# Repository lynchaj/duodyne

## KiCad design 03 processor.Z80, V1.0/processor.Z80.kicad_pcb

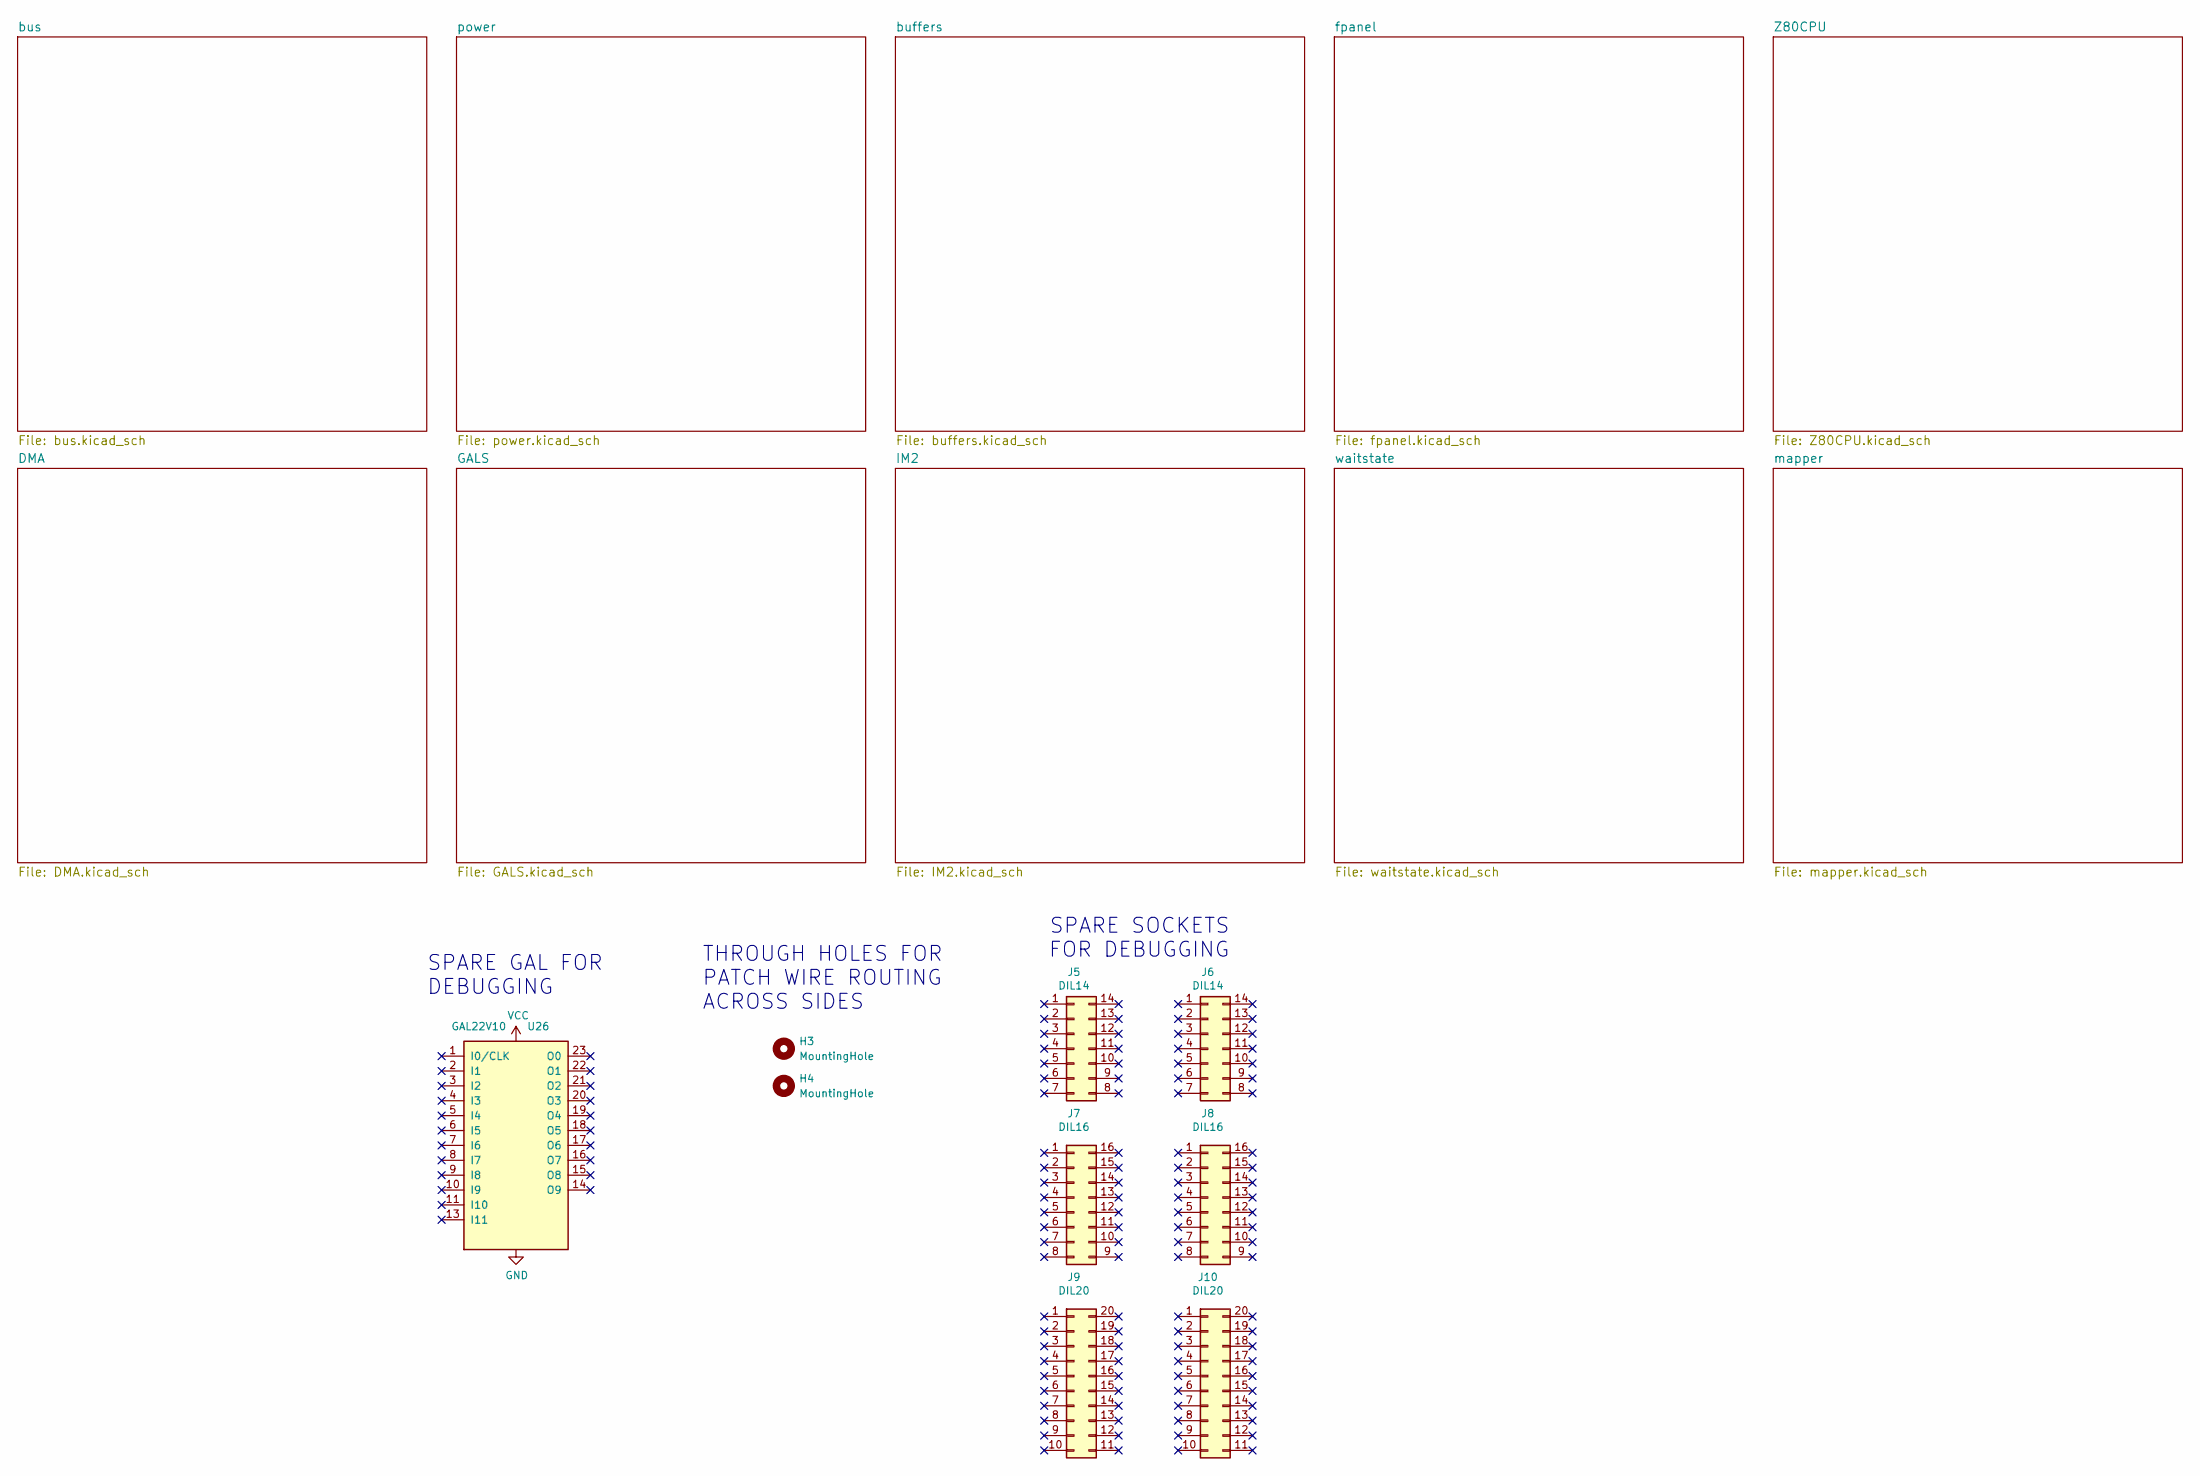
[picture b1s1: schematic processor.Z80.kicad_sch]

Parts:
H3, H4: MountingHole; MountingHole_2.2mm_M2_DIN965_Pad
J5, J6: DIL14; DIP-14_W7.62mm
J7, J8: DIL16; DIP-16_W7.62mm
J9, J10: DIL20; DIP-20_W7.62mm
U26: GAL22V10; DIP-24_W7.62mm

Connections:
GND: U26.12 (GND); also elsewhere on the board
VCC: U26.24 (VCC); also elsewhere on the board

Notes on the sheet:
THROUGH HOLES FOR PATCH WIRE ROUTING ACROSS SIDES
SPARE GAL FOR DEBUGGING
SPARE SOCKETS FOR DEBUGGING

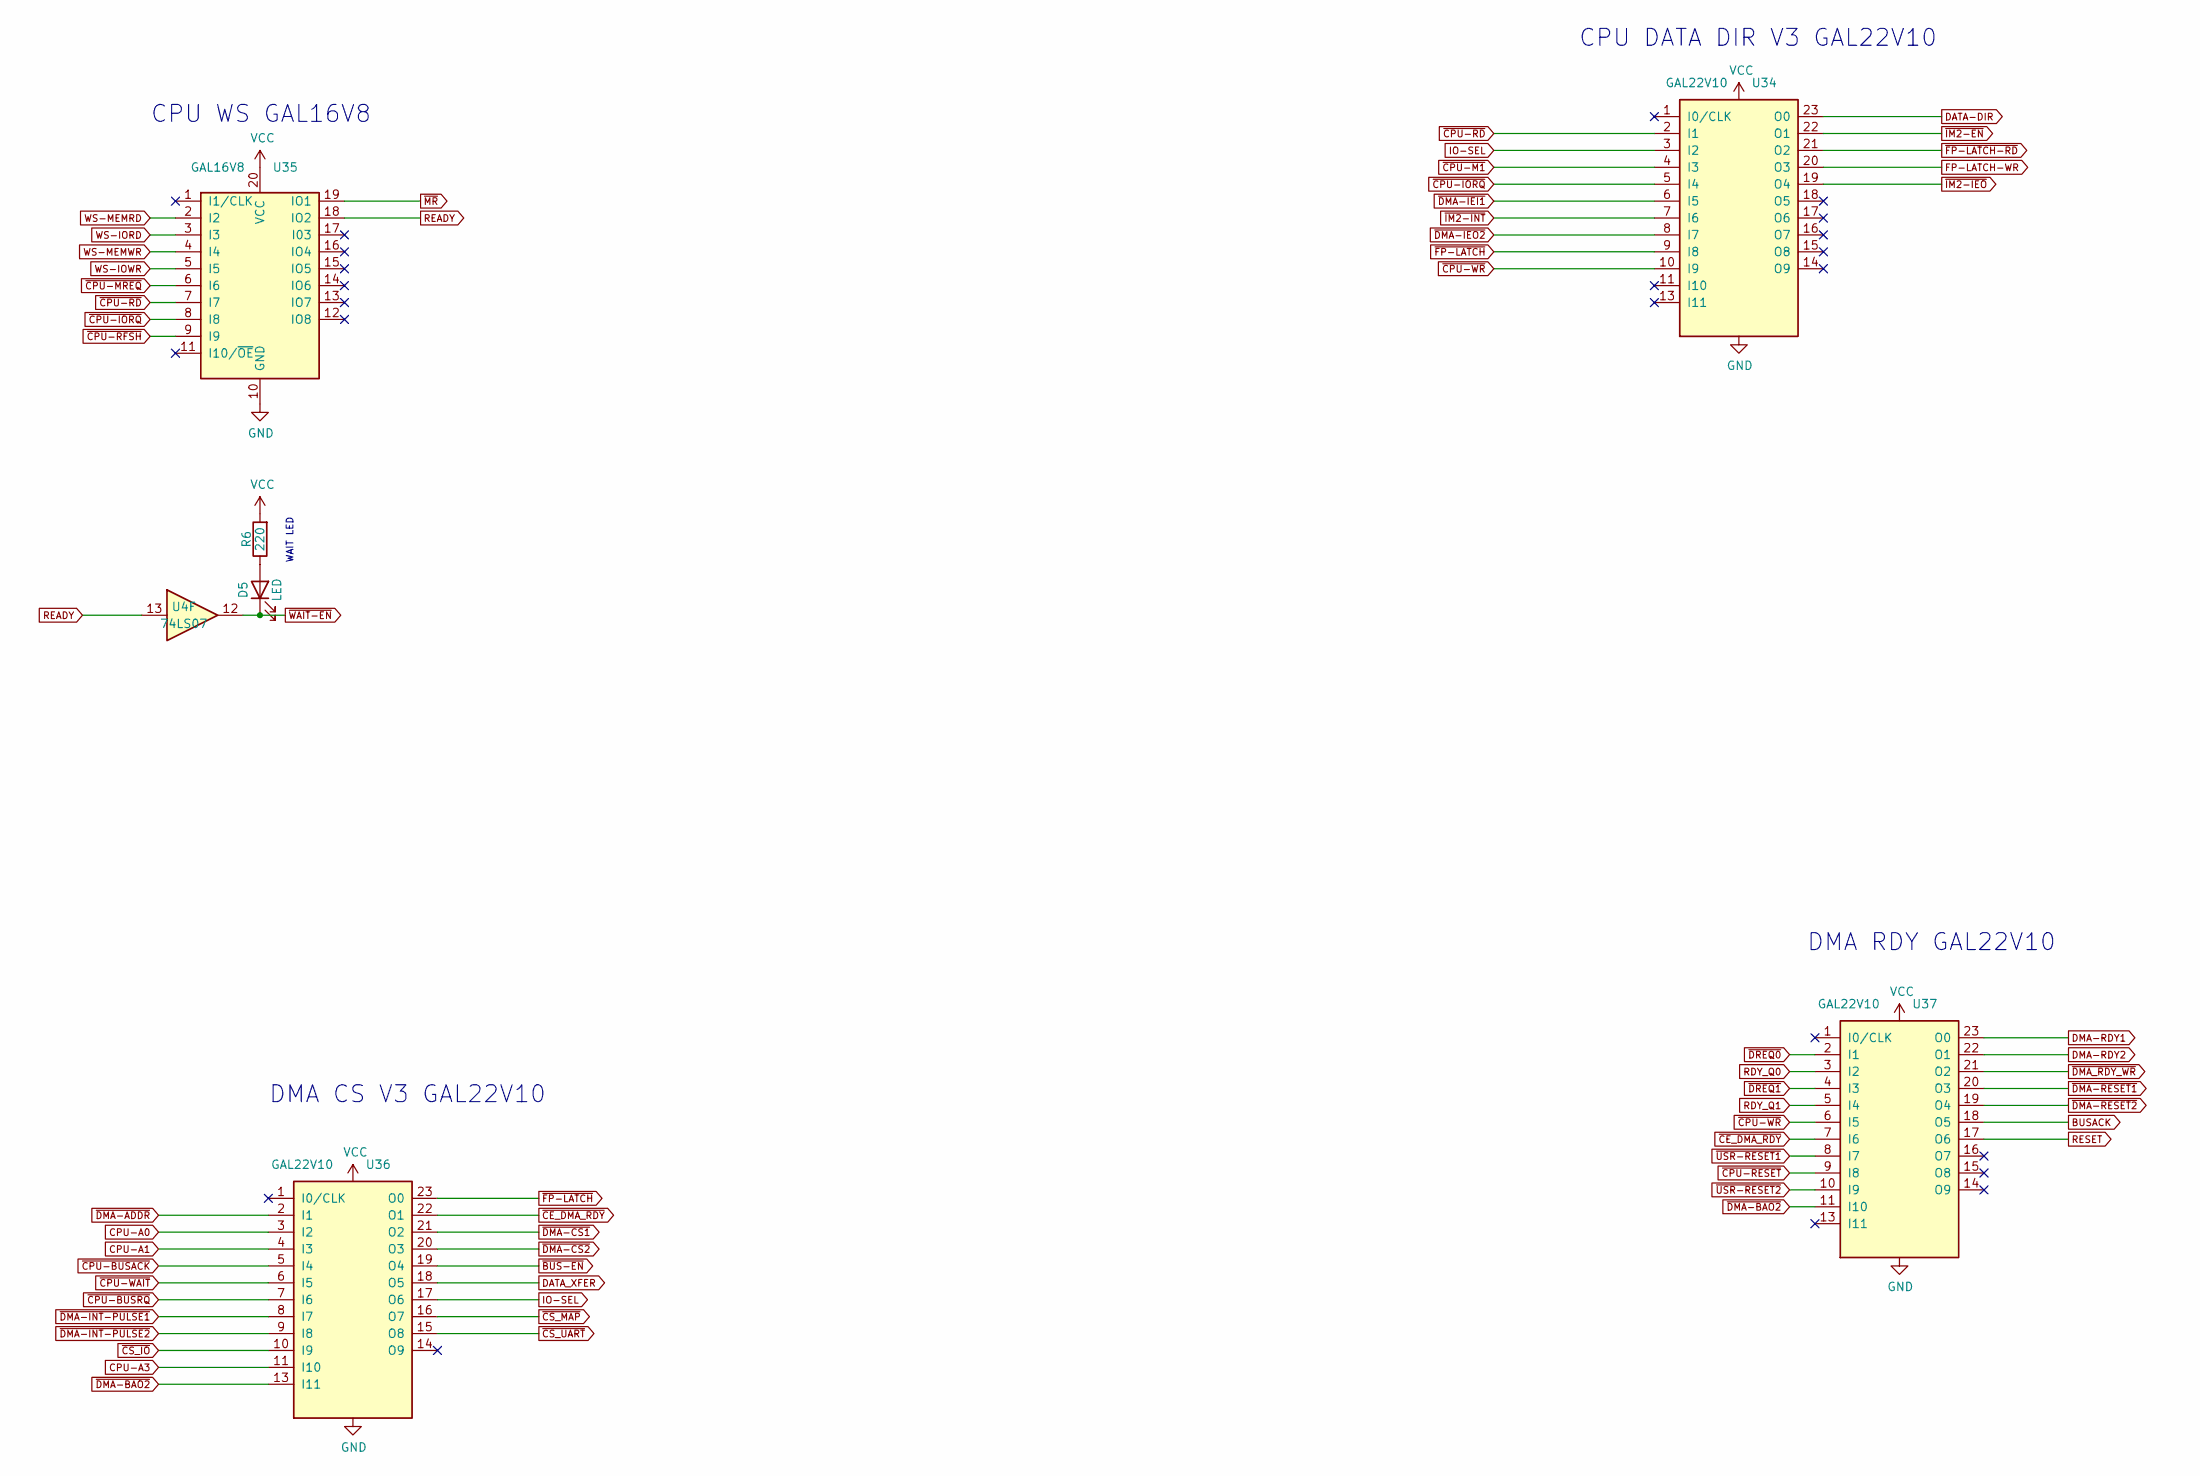
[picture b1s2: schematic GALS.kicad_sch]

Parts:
D5: LED; LED_D3.0mm_Horizontal_O3.81mm_Z2.0mm
R6: 220; R_Axial_DIN0207_L6.3mm_D2.5mm_P7.62mm_Horizontal
U4: 74LS07; DIP-14_W7.62mm
U34, U36, U37: GAL22V10; DIP-24_W7.62mm
U35: GAL16V8; DIP-20_W7.62mm

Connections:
BUSACK: U37.18 (O5); also elsewhere on the board
CPU-A0: U36.3 (I2); also elsewhere on the board
CPU-A1: U36.4 (I3); also elsewhere on the board
CPU-A3: U36.11 (I10); also elsewhere on the board
DATA-DIR: U34.23 (O0); also elsewhere on the board
DATA_XFER: U36.18 (O5); also elsewhere on the board
DMA-RDY1: U37.23 (O0); also elsewhere on the board
DMA-RDY2: U37.22 (O1); also elsewhere on the board
FP-LATCH-WR: U34.20 (O3); also elsewhere on the board
GND: U34.12 (GND), U35.10 (GND), U36.12 (GND), U37.12 (GND); also elsewhere on the board
IO-SEL: U34.3 (I2), U36.17 (O6)
unnamed: D5.2 (A), R6.1
RDY_Q0: U37.3 (I2); also elsewhere on the board
RDY_Q1: U37.5 (I4); also elsewhere on the board
READY: U4.13, U35.18 (IO2)
RESET: U37.17 (O6); also elsewhere on the board
VCC: R6.2, U34.24 (VCC), U35.20 (VCC), U36.24 (VCC), U37.24 (VCC); also elsewhere on the board
WS-IORD: U35.3 (I3); also elsewhere on the board
WS-IOWR: U35.5 (I5); also elsewhere on the board
WS-MEMRD: U35.2 (I2); also elsewhere on the board
WS-MEMWR: U35.4 (I4); also elsewhere on the board
~BUS-EN: U36.19 (O4); also elsewhere on the board
~CE_DMA_RDY: U36.22 (O1), U37.7 (I6)
~CPU-BUSACK: U36.5 (I4); also elsewhere on the board
~CPU-BUSRQ: U36.7 (I6); also elsewhere on the board
~CPU-IORQ: U34.5 (I4), U35.8 (I8); also elsewhere on the board
~CPU-M1: U34.4 (I3); also elsewhere on the board
~CPU-MREQ: U35.6 (I6); also elsewhere on the board
~CPU-RD: U34.2 (I1), U35.7 (I7); also elsewhere on the board
~CPU-RESET: U37.9 (I8); also elsewhere on the board
~CPU-RFSH: U35.9 (I9); also elsewhere on the board
~CPU-WAIT: U36.6 (I5); also elsewhere on the board
~CPU-WR: U34.10 (I9), U37.6 (I5); also elsewhere on the board
~CS_IO: U36.10 (I9); also elsewhere on the board
~CS_MAP: U36.16 (O7); also elsewhere on the board
~DMA-ADDR: U36.2 (I1); also elsewhere on the board
~DMA-BAO2: U36.13 (I11), U37.11 (I10); also elsewhere on the board
~DMA-CS1: U36.21 (O2); also elsewhere on the board
~DMA-CS2: U36.20 (O3); also elsewhere on the board
~DMA-IEI1: U34.6 (I5); also elsewhere on the board
~DMA-IEO2: U34.8 (I7); also elsewhere on the board
~DMA-INT-PULSE1: U36.8 (I7); also elsewhere on the board
~DMA-INT-PULSE2: U36.9 (I8); also elsewhere on the board
~DMA-RESET1: U37.20 (O3); also elsewhere on the board
~DMA-RESET2: U37.19 (O4); also elsewhere on the board
~DMA_RDY_WR: U37.21 (O2); also elsewhere on the board
~DREQ0: U37.2 (I1); also elsewhere on the board
~DREQ1: U37.4 (I3); also elsewhere on the board
~FP-LATCH-RD: U34.21 (O2); also elsewhere on the board
~FP-LATCH: U34.9 (I8), U36.23 (O0)
~IM2-EN: U34.22 (O1); also elsewhere on the board
~IM2-IEO: U34.19 (O4); also elsewhere on the board
~IM2-INT: U34.7 (I6); also elsewhere on the board
~MR: U35.19 (IO1); also elsewhere on the board
~USR-RESET1: U37.8 (I7); also elsewhere on the board
~USR-RESET2: U37.10 (I9); also elsewhere on the board
~WAIT-EN: D5.1 (K), U4.12; also elsewhere on the board

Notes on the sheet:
DMA CS V3 GAL22V10
DMA RDY GAL22V10
CPU WS GAL16V8
CPU DATA DIR V3 GAL22V10
WAIT LED

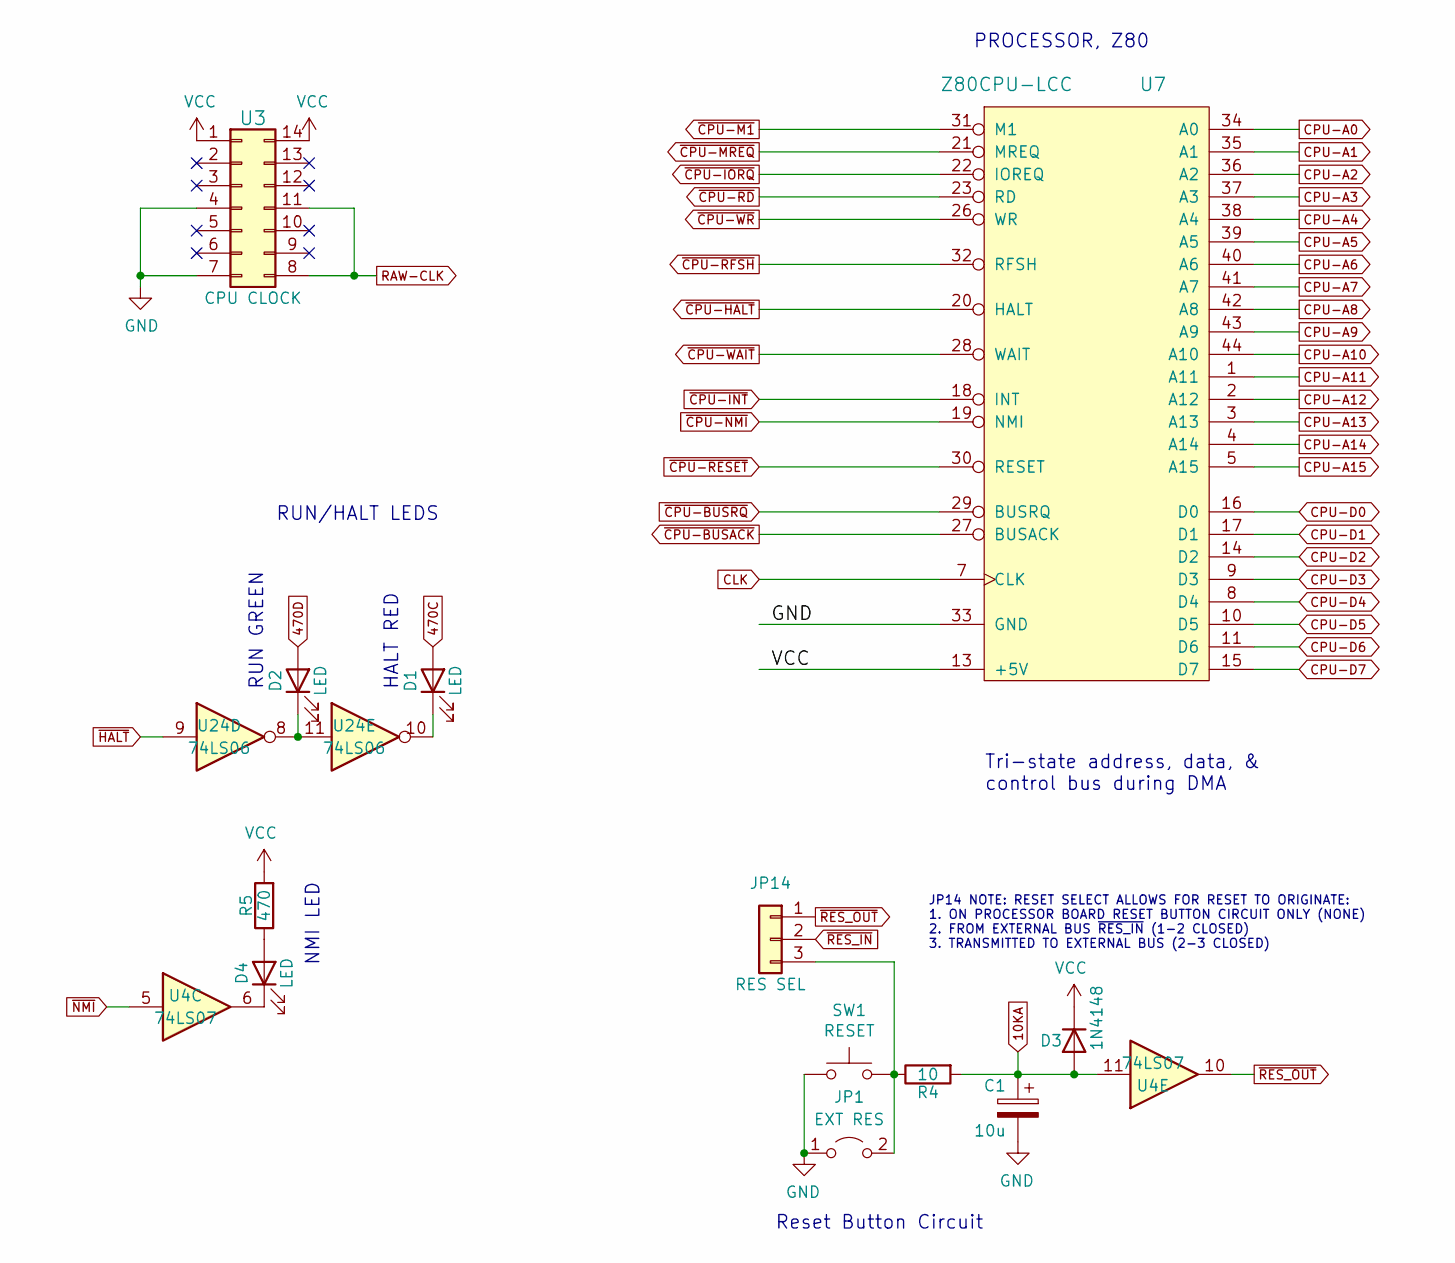
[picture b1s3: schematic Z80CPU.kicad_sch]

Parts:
C1: 10u; CP_Radial_D5.0mm_P2.50mm
D1, D2, D4: LED; LED_D3.0mm_Horizontal_O3.81mm_Z2.0mm
D3: 1N4148; D_DO-35_SOD27_P7.62mm_Horizontal
JP1: EXT RES; PinHeader_1x02_P2.54mm_Horizontal
JP14: RES SEL; PinHeader_1x03_P2.54mm_Vertical
R4: 10; R_Axial_DIN0207_L6.3mm_D2.5mm_P7.62mm_Horizontal
R5: 470; R_Axial_DIN0207_L6.3mm_D2.5mm_P7.62mm_Horizontal
SW1: RESET; SW_Tactile_SPST_Angled_PTS645Vx58-2LFS
U3: CPU CLOCK; DIP-14_W7.62mm
U4: 74LS07; DIP-14_W7.62mm
U7: Z80CPU-LCC; PLCC-44_THT-Socket; Manufacturer_Part_Number Z84C00
U24: 74LS06

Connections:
10KA: C1.1, D3.2 (A), R4.2, U4.11; also elsewhere on the board
470C: D1.2 (A); also elsewhere on the board
470D: D2.2 (A); also elsewhere on the board
CLK: U7.7 (CLK); also elsewhere on the board
CPU-A0: U7.34 (A0); also elsewhere on the board
CPU-A1: U7.35 (A1); also elsewhere on the board
CPU-A2: U7.36 (A2); also elsewhere on the board
CPU-A3: U7.37 (A3); also elsewhere on the board
CPU-A4: U7.38 (A4); also elsewhere on the board
CPU-A5: U7.39 (A5); also elsewhere on the board
CPU-A6: U7.40 (A6); also elsewhere on the board
CPU-A7: U7.41 (A7); also elsewhere on the board
CPU-A8: U7.42 (A8); also elsewhere on the board
CPU-A9: U7.43 (A9); also elsewhere on the board
CPU-A10: U7.44 (A10); also elsewhere on the board
CPU-A11: U7.1 (A11); also elsewhere on the board
CPU-A12: U7.2 (A12); also elsewhere on the board
CPU-A13: U7.3 (A13); also elsewhere on the board
CPU-A14: U7.4 (A14); also elsewhere on the board
CPU-A15: U7.5 (A15); also elsewhere on the board
CPU-D0: U7.16 (D0); also elsewhere on the board
CPU-D1: U7.17 (D1); also elsewhere on the board
CPU-D2: U7.14 (D2); also elsewhere on the board
CPU-D3: U7.9 (D3); also elsewhere on the board
CPU-D4: U7.8 (D4); also elsewhere on the board
CPU-D5: U7.10 (D5); also elsewhere on the board
CPU-D6: U7.11 (D6); also elsewhere on the board
CPU-D7: U7.15 (D7); also elsewhere on the board
GND: C1.2, JP1.1 (A), SW1.2, U3.4, U3.7, U7.33 (GND); also elsewhere on the board
unnamed: D1.1 (K), U24.10
unnamed: D2.1 (K), U24.8, U24.11
unnamed: D4.1 (K), U4.6
unnamed: D4.2 (A), R5.1
RAW-CLK: U3.8, U3.11; also elsewhere on the board
VCC: D3.1 (K), R5.2, U3.1, U3.14, U7.13 (+5V); also elsewhere on the board
~CPU-BUSACK: U7.27 (BUSACK); also elsewhere on the board
~CPU-BUSRQ: U7.29 (BUSRQ); also elsewhere on the board
~CPU-HALT: U7.20 (HALT); also elsewhere on the board
~CPU-INT: U7.18 (INT); also elsewhere on the board
~CPU-IORQ: U7.22 (IOREQ); also elsewhere on the board
~CPU-M1: U7.31 (M1); also elsewhere on the board
~CPU-MREQ: U7.21 (MREQ); also elsewhere on the board
~CPU-NMI: U7.19 (NMI); also elsewhere on the board
~CPU-RD: U7.23 (RD); also elsewhere on the board
~CPU-RESET: U7.30 (RESET); also elsewhere on the board
~CPU-RFSH: U7.32 (RFSH); also elsewhere on the board
~CPU-WAIT: U7.28 (WAIT); also elsewhere on the board
~CPU-WR: U7.26 (WR); also elsewhere on the board
~HALT: U24.9; also elsewhere on the board
~NMI: U4.5; also elsewhere on the board
~RES_IN: JP14.2; also elsewhere on the board
~RES_OUT: JP14.1, U4.10; also elsewhere on the board

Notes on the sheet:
RUN GREEN
JP14 NOTE: RESET SELECT ALLOWS FOR RESET TO ORIGINATE: 1. ON PROCESSOR BOARD RESET BUTTON CIRCUIT ONLY (NONE) 2. FROM EXTERNAL BUS ~{RES_IN} (1-2 CLOSED) 3. TRANSMITTED TO EXTERNAL BUS (2-3 CLOSED)
HALT RED
Reset Button Circuit
NMI LED
PROCESSOR, Z80
Tri-state address, data, & control bus during DMA
RUN/HALT LEDS

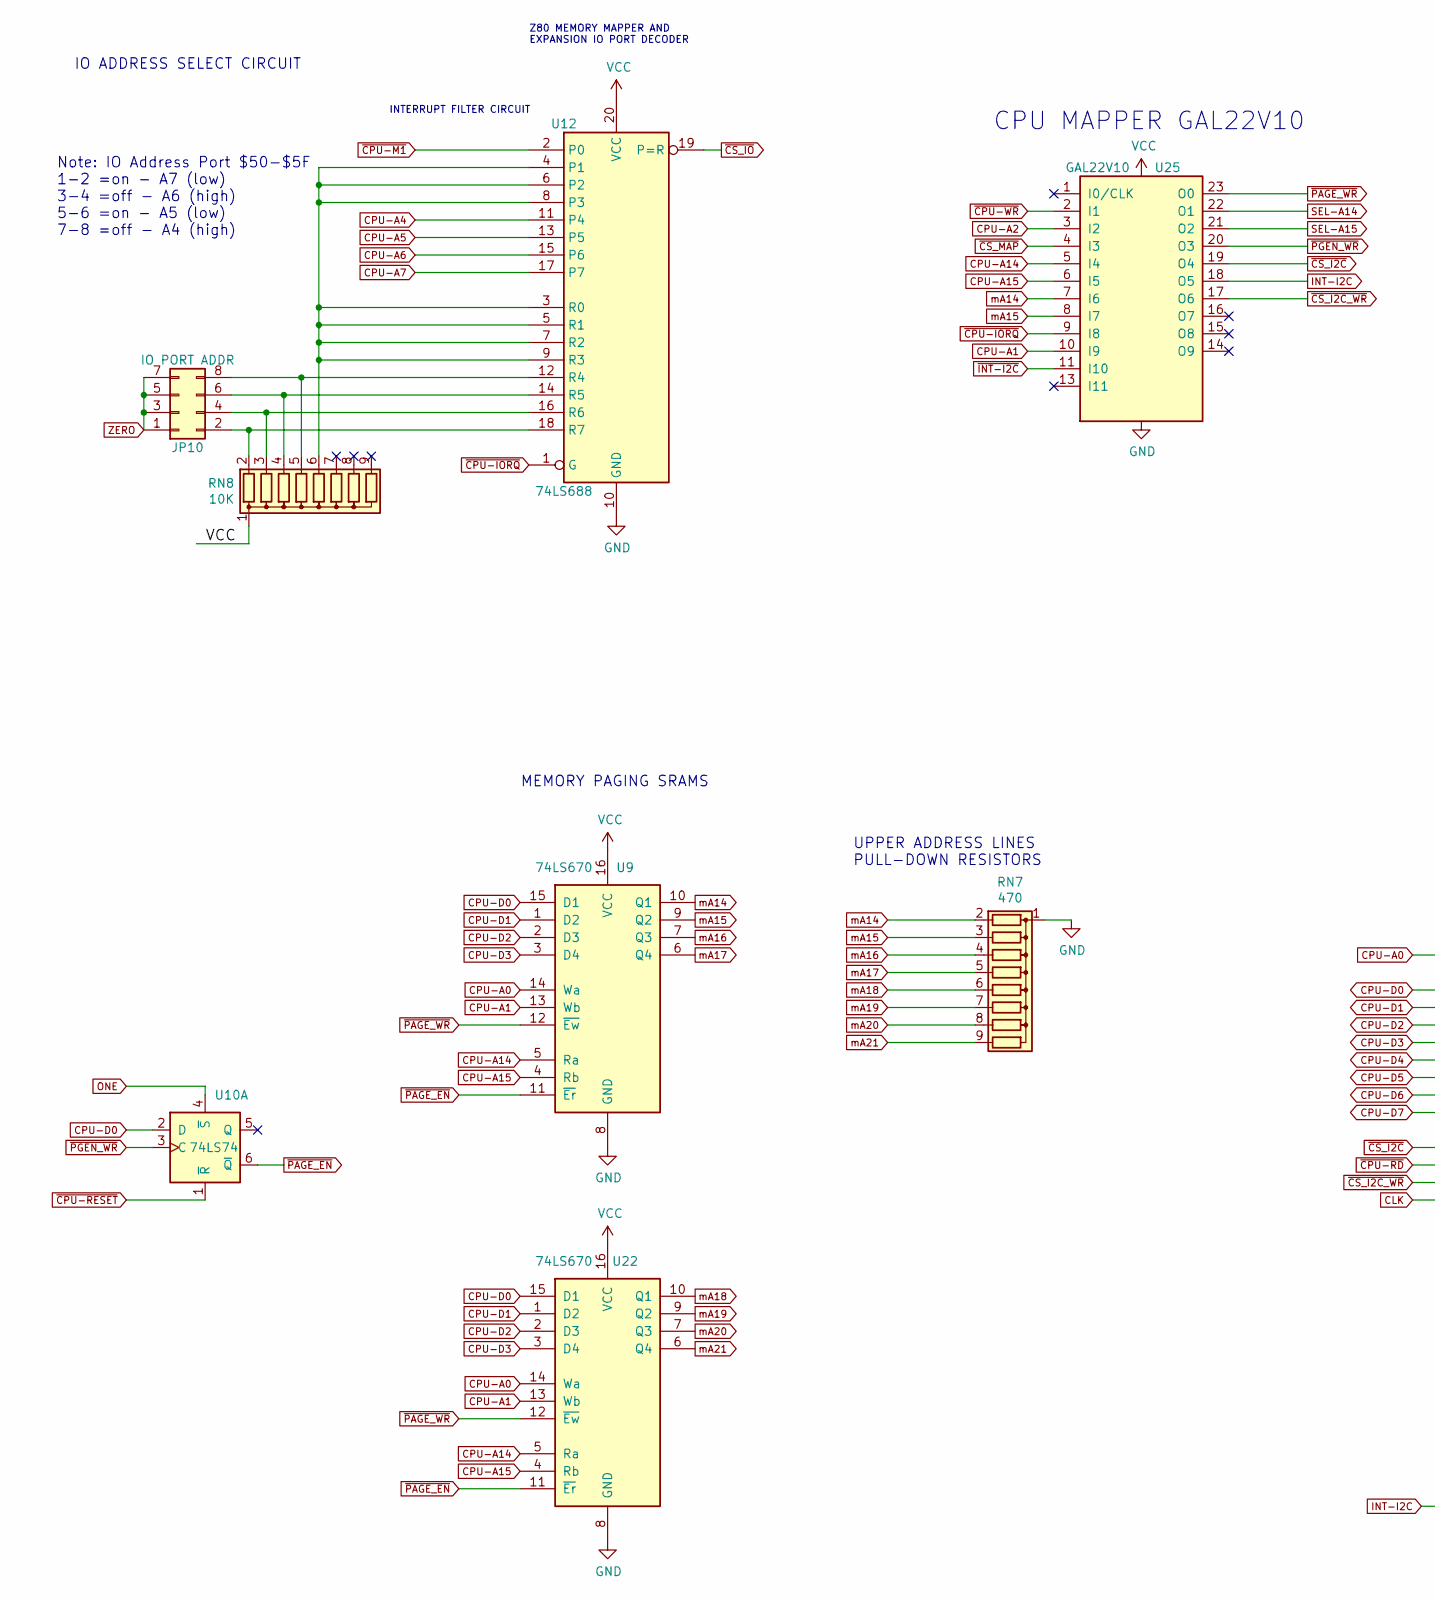
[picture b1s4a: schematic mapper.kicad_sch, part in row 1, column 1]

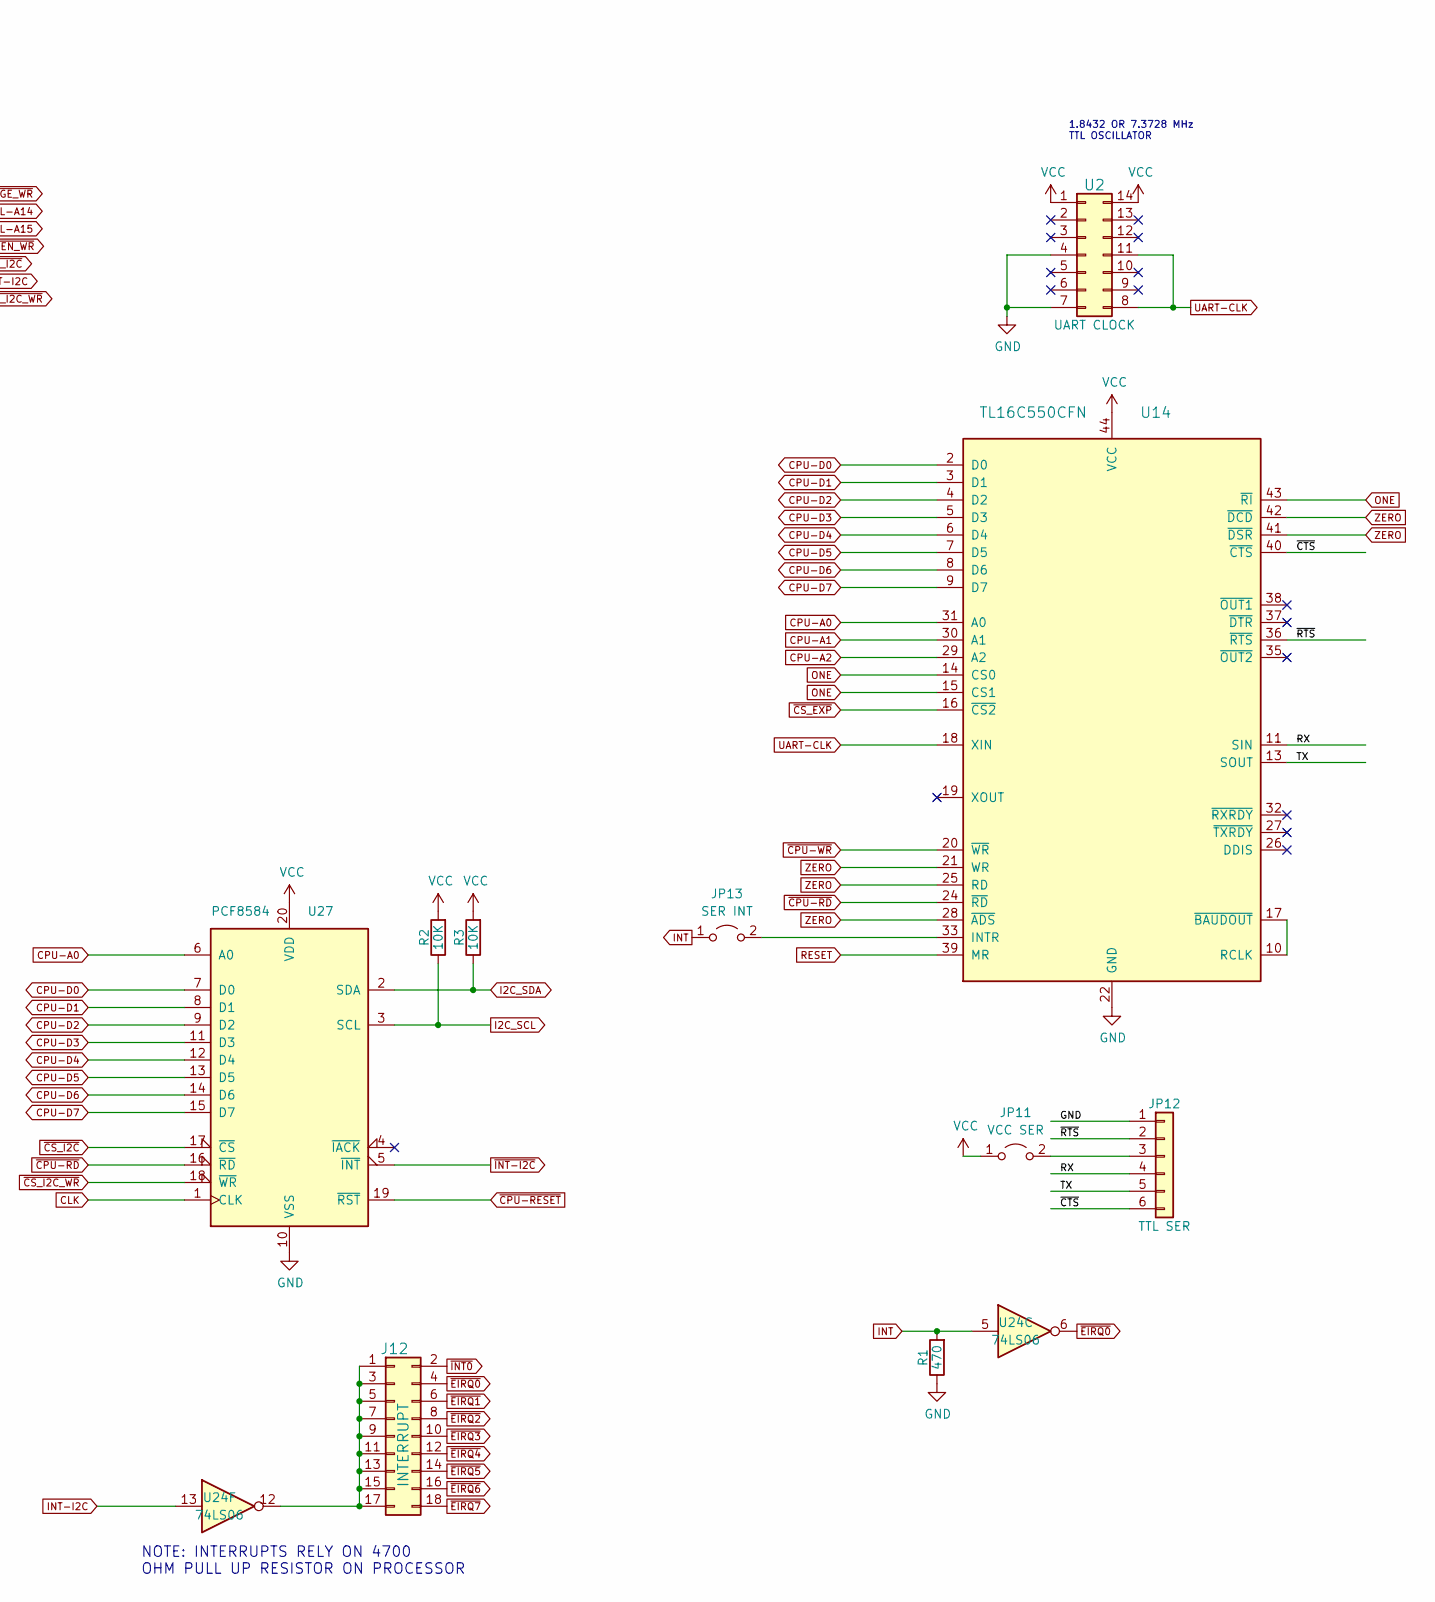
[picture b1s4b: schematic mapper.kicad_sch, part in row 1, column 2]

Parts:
J12: INTERRUPT; PinHeader_2x09_P2.54mm_Vertical
JP10: IO PORT ADDR; PinHeader_2x04_P2.54mm_Vertical
JP11: VCC SER; PinHeader_1x02_P2.54mm_Vertical
JP12: TTL SER; PinHeader_1x06_P2.54mm_Vertical
JP13: SER INT; PinHeader_1x02_P2.54mm_Vertical
R1: 470; R_Axial_DIN0207_L6.3mm_D2.5mm_P7.62mm_Horizontal
R2, R3: 10K; R_Axial_DIN0207_L6.3mm_D2.5mm_P7.62mm_Horizontal
RN7: 470; R_Array_SIP9
RN8: 10K; R_Array_SIP9
U2: UART CLOCK; DIP-14_W7.62mm
U9, U22: 74LS670; DIP-16_W7.62mm
U10: 74LS74; DIP-14_W7.62mm
U12: 74LS688; DIP-20_W7.62mm
U14: TL16C550CFN; PLCC-44_THT-Socket
U24: 74LS06
U25: GAL22V10; DIP-24_W7.62mm
U27: PCF8584; DIP-20_W7.62mm

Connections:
CLK: U27.1 (CLK); also elsewhere on the board
CPU-A0: U9.14 (Wa), U14.31 (A0), U22.14 (Wa), U27.6 (A0); also elsewhere on the board
CPU-A1: U9.13 (Wb), U14.30 (A1), U22.13 (Wb), U25.10 (I9); also elsewhere on the board
CPU-A2: U14.29 (A2), U25.3 (I2); also elsewhere on the board
CPU-A4: U12.11 (P4); also elsewhere on the board
CPU-A5: U12.13 (P5); also elsewhere on the board
CPU-A6: U12.15 (P6); also elsewhere on the board
CPU-A7: U12.17 (P7); also elsewhere on the board
CPU-A14: U9.5 (Ra), U22.5 (Ra), U25.5 (I4); also elsewhere on the board
CPU-A15: U9.4 (Rb), U22.4 (Rb), U25.6 (I5); also elsewhere on the board
CPU-D0: U9.15 (D1), U10.2 (D), U14.2 (D0), U22.15 (D1), U27.7 (D0); also elsewhere on the board
CPU-D1: U9.1 (D2), U14.3 (D1), U22.1 (D2), U27.8 (D1); also elsewhere on the board
CPU-D2: U9.2 (D3), U14.4 (D2), U22.2 (D3), U27.9 (D2); also elsewhere on the board
CPU-D3: U9.3 (D4), U14.5 (D3), U22.3 (D4), U27.11 (D3); also elsewhere on the board
CPU-D4: U14.6 (D4), U27.12 (D4); also elsewhere on the board
CPU-D5: U14.7 (D5), U27.13 (D5); also elsewhere on the board
CPU-D6: U14.8 (D6), U27.14 (D6); also elsewhere on the board
CPU-D7: U14.9 (D7), U27.15 (D7); also elsewhere on the board
GND: R1.1, RN7.1 (common), U2.4, U2.7, U9.8 (GND), U12.10 (GND), U14.22 (GND), U22.8 (GND), U25.12 (GND), U27.10 (VSS); also elsewhere on the board
I2C_SCL: R2.1, U27.3 (SCL); also elsewhere on the board
I2C_SDA: R3.1, U27.2 (SDA); also elsewhere on the board
INT: JP13.1 (A), R1.2, U24.5
INT-I2C: U24.13, U25.18 (O5)
unnamed: J12.1, J12.3, J12.5, J12.7, J12.9, J12.11, J12.13, J12.15, J12.17, U24.12
unnamed: JP10.2, RN8.2 (R1), U12.18 (R7)
unnamed: JP10.4, RN8.3 (R2), U12.16 (R6)
unnamed: JP10.6, RN8.4 (R3), U12.14 (R5)
unnamed: JP10.8, RN8.5 (R4), U12.12 (R4)
unnamed: JP11.2 (B), JP12.3
unnamed: JP13.2 (B), U14.33 (INTR)
unnamed: RN8.6 (R5), U12.3 (R0), U12.4 (P1), U12.5 (R1), U12.6 (P2), U12.7 (R2), U12.8 (P3), U12.9 (R3)
unnamed: U14.10 (RCLK), U14.17 (~BAUDOUT)
ONE: U10.4 (~S), U14.14 (CS0), U14.15 (CS1), U14.43 (~RI); also elsewhere on the board
RESET: U14.39 (MR); also elsewhere on the board
RX: JP12.4, U14.11 (SIN); also elsewhere on the board
SEL-A14: U25.22 (O1); also elsewhere on the board
SEL-A15: U25.21 (O2); also elsewhere on the board
TX: JP12.5, U14.13 (SOUT); also elsewhere on the board
UART-CLK: U2.8, U2.11, U14.18 (XIN)
VCC: JP11.1 (A), R2.2, R3.2, RN8.1 (common), U2.1, U2.14, U9.16 (VCC), U12.20 (VCC), U14.44 (VCC), U22.16 (VCC), U25.24 (VCC), U27.20 (VDD); also elsewhere on the board
ZERO: JP10.1, JP10.3, JP10.5, JP10.7, U14.21 (WR), U14.25 (RD), U14.28 (~ADS), U14.41 (~DSR), U14.42 (~DCD); also elsewhere on the board
mA14: RN7.2 (R1), U9.10 (Q1), U25.7 (I6)
mA15: RN7.3 (R2), U9.9 (Q2), U25.8 (I7)
mA16: RN7.4 (R3), U9.7 (Q3); also elsewhere on the board
mA17: RN7.5 (R4), U9.6 (Q4); also elsewhere on the board
mA18: RN7.6 (R5), U22.10 (Q1); also elsewhere on the board
mA19: RN7.7 (R6), U22.9 (Q2); also elsewhere on the board
mA20: RN7.8 (R7), U22.7 (Q3); also elsewhere on the board
mA21: RN7.9 (R8), U22.6 (Q4); also elsewhere on the board
~AxPRIME: U25.13 (I11), U25.14 (O9)
~CPU-IORQ: U12.1 (G), U25.9 (I8); also elsewhere on the board
~CPU-M1: U12.2 (P0); also elsewhere on the board
~CPU-RD: U14.24 (~RD), U27.16 (~RD); also elsewhere on the board
~CPU-RESET: U10.1 (~R), U27.19 (~RST); also elsewhere on the board
~CPU-WR: U14.20 (~WR), U25.2 (I1); also elsewhere on the board
~CS_I2C_WR: U25.17 (O6), U27.18 (~WR)
~CS_I2C: U25.19 (O4), U27.17 (~CS)
~CS_IO: U12.19 (P=R); also elsewhere on the board
~CS_MAP: U25.4 (I3); also elsewhere on the board
~CTS: JP12.6, U14.40 (~CTS); also elsewhere on the board
~EIRQ0: J12.4, U24.6; also elsewhere on the board
~EIRQ1: J12.6; also elsewhere on the board
~EIRQ2: J12.8; also elsewhere on the board
~EIRQ3: J12.10; also elsewhere on the board
~EIRQ4: J12.12; also elsewhere on the board
~EIRQ5: J12.14; also elsewhere on the board
~EIRQ6: J12.16; also elsewhere on the board
~EIRQ7: J12.18; also elsewhere on the board
~INT0: J12.2; also elsewhere on the board
~INT-I2C: U25.11 (I10), U27.5 (~INT); also elsewhere on the board
~PAGE_EN: U9.11 (~Er), U10.6 (~Q), U22.11 (~Er)
~PAGE_WR: U9.12 (~Ew), U22.12 (~Ew), U25.23 (O0)
~PGEN_WR: U10.3 (C), U25.20 (O3)
~RTS: JP12.2, U14.36 (~RTS); also elsewhere on the board

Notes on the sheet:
CPU MAPPER GAL22V10
Z80 MEMORY MAPPER AND EXPANSION IO PORT DECODER
UPPER ADDRESS LINES PULL-DOWN RESISTORS
MEMORY PAGING SRAMS
IO ADDRESS SELECT CIRCUIT
INTERRUPT FILTER CIRCUIT
1.8432 OR 7.3728 MHz TTL OSCILLATOR
NOTE: INTERRUPTS RELY ON 4700 OHM PULL UP RESISTOR ON PROCESSOR
Note: IO Address Port $50-$5F 1-2 =on - A7 (low) 3-4 =off - A6 (high) 5-6 =on - A5 (low) 7-8 =off - A4 (high)
